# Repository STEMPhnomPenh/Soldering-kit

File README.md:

# Soldering-kit
Production files for the 3-in-1 soldering kit project

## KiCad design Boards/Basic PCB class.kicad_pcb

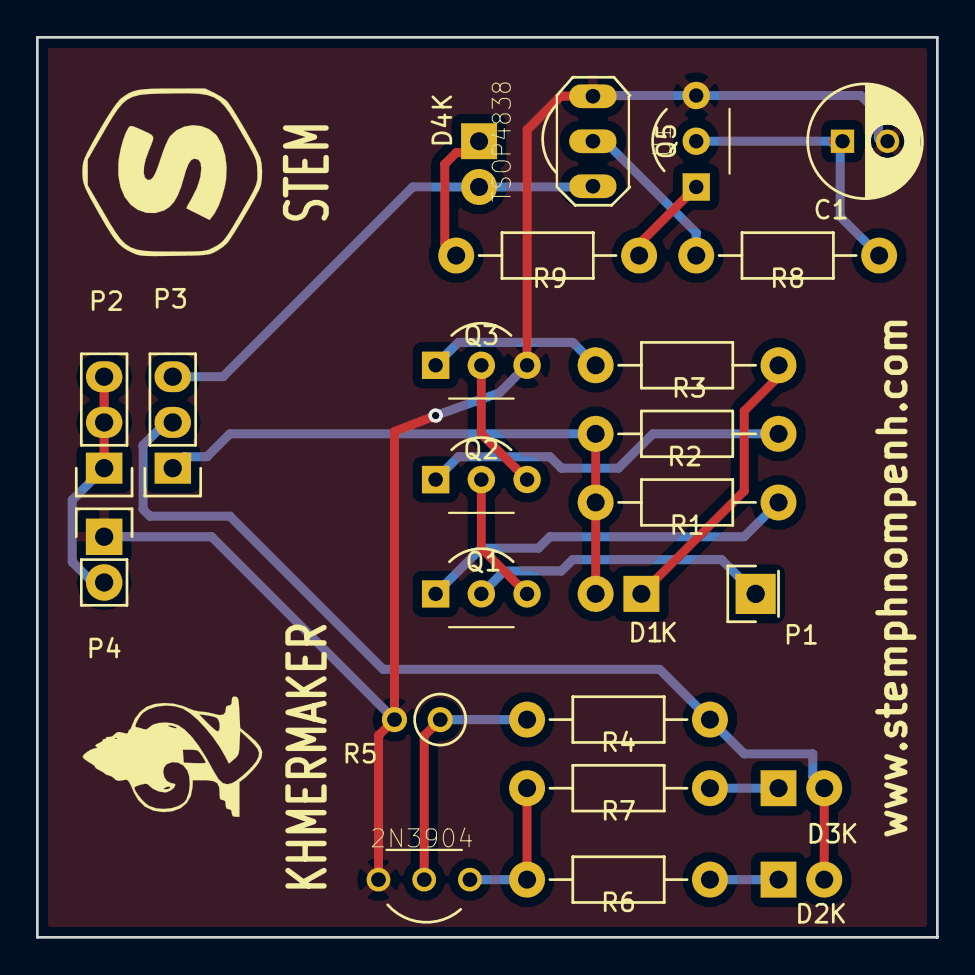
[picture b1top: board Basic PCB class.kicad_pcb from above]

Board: 2 copper layers, 50.0 x 50.0 mm, 24 parts (0 on the bottom side), 20 nets.

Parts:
C1: 10u; C_Radial_D6.3_L11.2_P2.5
D1, D2, D3, D4: LED; LED-3MM
P1: ATEN; Socket_Strip_Straight_1x01
P2: VSS; Socket_Strip_Straight_1x03
P3: CS; Socket_Strip_Straight_1x03
P4: PW; Socket_Strip_Straight_1x02
Q1, Q2, Q3, Q5: BC547; TO-92_Inline_Wide
Q4: 2N3904; 2n3904
R1: 1M; Resistor_Horizontal_RM10mm
R2: 100K; Resistor_Horizontal_RM10mm
R3, R6, R7, R9: 220; Resistor_Horizontal_RM10mm
R4: 47K; Resistor_Horizontal_RM10mm
R5: Photores; R1
R8: 1K; Resistor_Horizontal_RM10mm
U1: TSOP4838; TSOP48

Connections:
/GND: C1.2, P4.1, Q3.3, Q4.3, Q5.3, R5.2, U1.GND
/VSS: P2.1, P2.2, P2.3, P4.2
unnamed: C1.1, Q5.2, R8.1
unnamed: D1.1, R3.2
unnamed: D1.2, P3.1, R1.2, R2.2
unnamed: D2.1, R6.1
unnamed: D2.2, D3.2, P3.2, R4.1
unnamed: D3.1, R7.1
unnamed: D4.1, R9.1
unnamed: D4.2, P3.3, U1.VCC
unnamed: P1.1, Q1.2
unnamed: Q1.1, R1.1
unnamed: Q1.3, Q2.2
unnamed: Q2.1, R2.1
unnamed: Q2.3, Q3.2
unnamed: Q3.1, R3.1
unnamed: Q4.1, R6.2, R7.2
unnamed: Q4.2, R4.2, R5.1
unnamed: Q5.1, R9.2
unnamed: R8.2, U1.OUT

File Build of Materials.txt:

1 pin female header		=	1
1M Resistor			=	1
100K Resistor			=	1
220 Resistor			=	4
BC547 Transistor		=	4
3mm LED				=	4
LDR / Photo Resistor		= 	1
47K Resistor			=	1
2N3904 Transistor		=	1
1K Resistor			=	1
10uf (electrolytic) cap		=	1
3 pins male header		=	2
2 pins female header		=	1
TSOP4838			=	1

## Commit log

2017-04-03 Adding files
    Adding files
2017-04-03 renaming
    avoid profanities!
